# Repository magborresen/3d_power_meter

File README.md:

# 3D Power Meter
Power Meter developed for use in 3D printers. Communicates with a Raspberry Pi over SPI from the ADC.
The Pi can then show the calculate and show power values based on the current received from the board.
Uses a Hall-effect sensor for current measurement.

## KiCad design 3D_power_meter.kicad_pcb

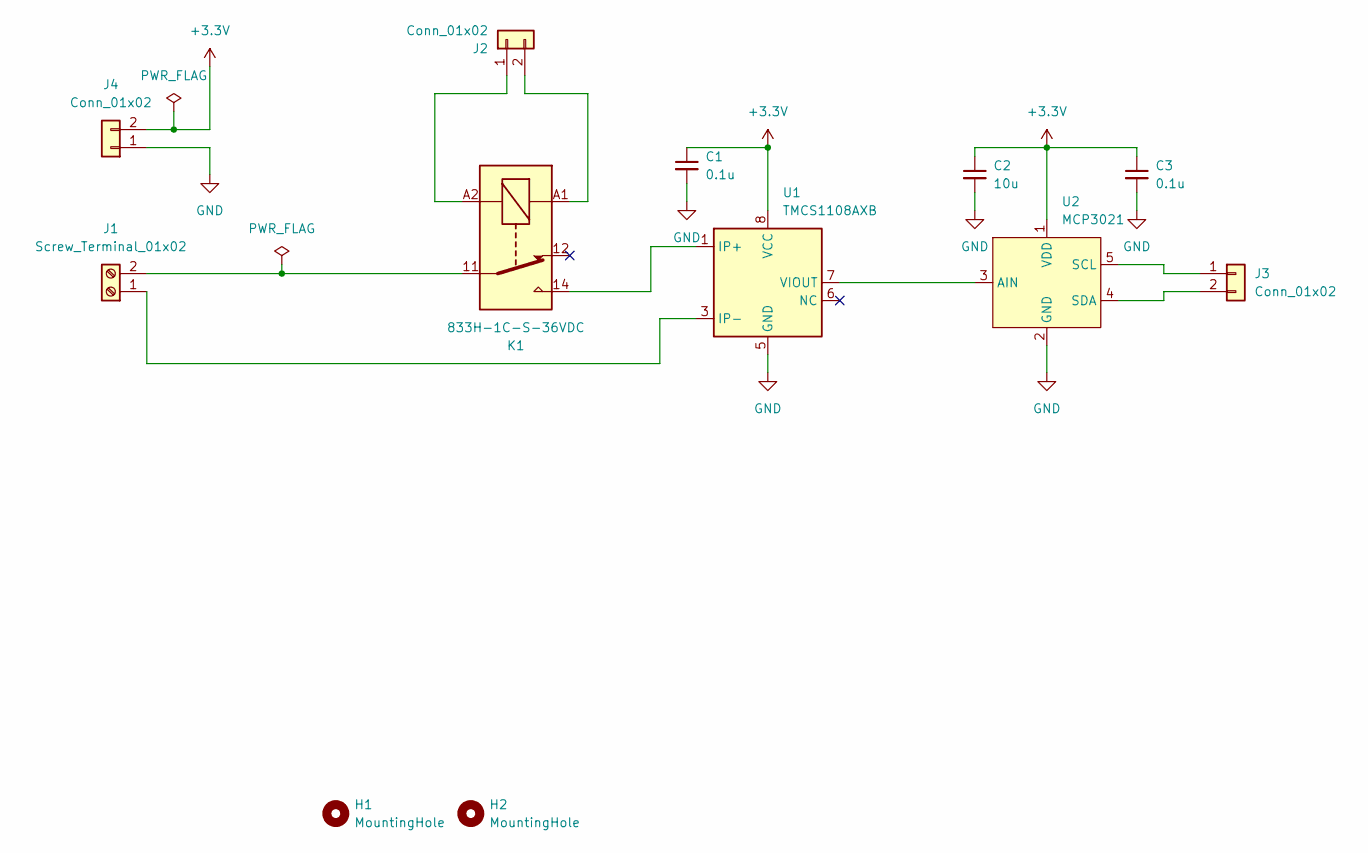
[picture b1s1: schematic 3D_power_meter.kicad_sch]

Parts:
C1, C3: 0.1u; C_0603_1608Metric_Pad1.08x0.95mm_HandSolder
C2: 10u; C_1206_3216Metric_Pad1.33x1.80mm_HandSolder
H1, H2: MountingHole; MountingHole_3.2mm_M3_ISO7380
J1: Screw_Terminal_01x02; TerminalBlock_Phoenix_MKDS-1,5-2-5.08_1x02_P5.08mm_Horizont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
J2, J3, J4: Conn_01x02; PinHeader_1x02_P2.54mm_Vertical
K1: 833H-1C-S-36VDC; Relay_SPDT_Finder_36.11
U1: TMCS1108AXB; SOIC-8_3.9x4.9mm_P1.27mm
U2: MCP3021; SOT-23-5_HandSoldering

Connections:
+3.3V: C1.1, C2.1, C3.1, J4.2, U1.8 (VCC), U2.1 (VDD)
GND: C1.2, C2.2, C3.2, J4.1, U1.5 (GND), U2.2 (GND)
unnamed: J1.1, U1.3 (IP-), U1.4 (IP-)
unnamed: J1.2, K1.11
unnamed: J2.1, K1.A2
unnamed: J2.2, K1.A1
unnamed: J3.1, U2.5 (SCL)
unnamed: J3.2, U2.4 (SDA)
unnamed: K1.14, U1.1 (IP+), U1.2 (IP+)
unnamed: U1.7 (VIOUT), U2.3 (AIN)

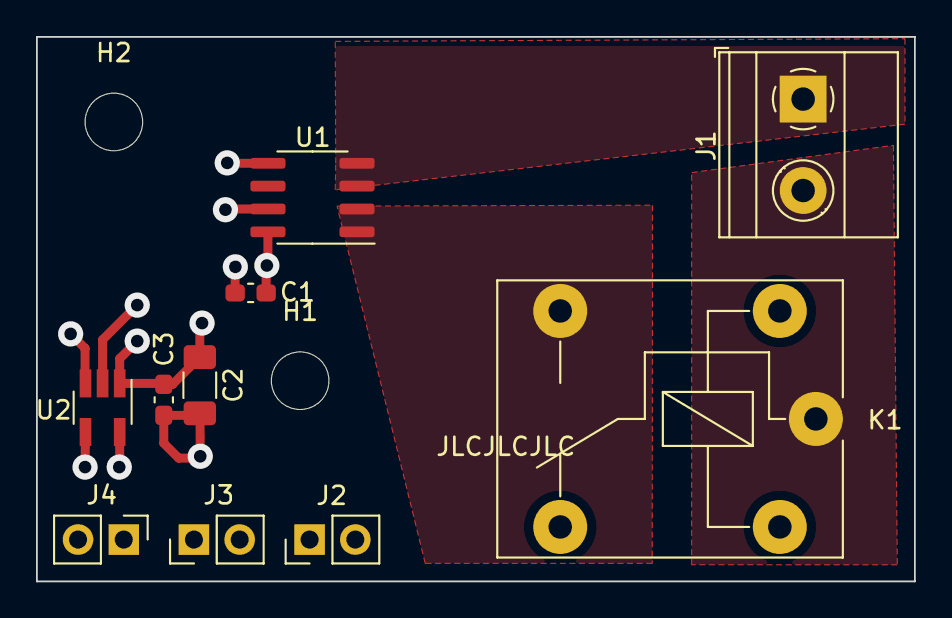
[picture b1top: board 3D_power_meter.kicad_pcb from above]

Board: 4 copper layers, 48.8 x 30.2 mm, 12 parts (0 on the bottom side), 10 nets.
